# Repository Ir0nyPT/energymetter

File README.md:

# energymetter
contador de energia

# Pre-requesitos
1. Gerar chave no computador para pedir acesso ao github. Após correr o comando, este irá perguntar o ficheiro onde guardar e pass a atribuir, clicar no "Enter" 3 vezes para avançar sem adicionar qualquer valor
> ssh-keygen -t rsa -b 4096

2. Imprimir no terminal a chave gerada
> cat ~/.ssh/id_rsa.pub 

3. Ir ao link abaixo e colar a chave imprimida no último comando no espaço "Key" (chave completa e sem qualquer alteração). Como Título é indiferente o que escreves
https://github.com/settings/ssh/new

4. Clonar o repositório
> git clone git@github.com:Ir0nyPT/energymetter.git

5. Instalar e inicializar 
> cd energymetter

> ./script.sh setup

> ./script.sh init

# Compilar e descarregar
> ./script.sh buildandcopy

OU 

> ./script.sh build

> ./script.sh copy

# Comando disponíveis no script

## Inicializar
> ./script.sh init

## Compilar
> ./script.sh build

## Apagar cache - util para recompilar
> ./script.sh clean

## Enviar para o Pico
> ./script.sh copy

## Obter um terminal de "Debug" (com a ferramenta Minicom)
### Iniciar terminal
> ./script.sh debug
### Terminar terminal
> Press CTRL+A X
### Dar comando para o rasp ir para modo de programação
Com o terminal de debug aberto escrever "reboot" e pressionar enter

# Como guardar algerações?
Antes de iniciar alguma alteração do programa cria um "ramo" do programa
> git checkout -b devop_mj

Após alterações feitas, para reter as alterações
> git add .

Para gravar as alterações. Alterar a "mensagem" por uma breve descrição do que fizes-te
> git commit -m "mensagem"

Para enviar para o github de forma a partilhar
> git push -u origin devop_mj

# Como atualizar com as alterações online?
Desta forma iras obter alterações que outros tenham feito
> git pull 

# Pico W LED
https://github.com/raspberrypi/pico-examples/blob/master/pico_w/wifi/blink/picow_blink.c

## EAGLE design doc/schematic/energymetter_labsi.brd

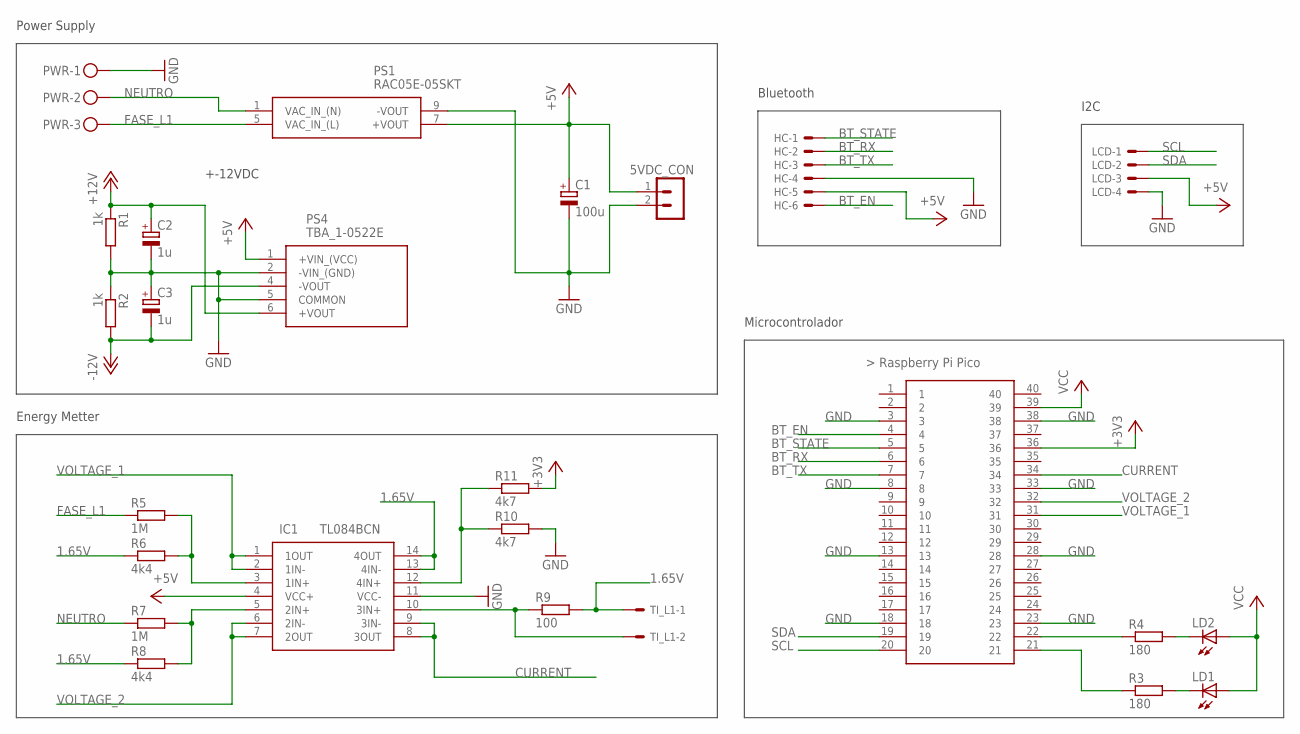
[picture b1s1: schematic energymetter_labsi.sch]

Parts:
5VDC_CON: MA02-1
C1: 100u; E2-5
C2, C3: 1u; E2-5
HC: 22-23-2061
IC1: TL084BCN; DIP794W53P254L1930H508Q14N
LCD: Display; 22-23-2041
LD1, LD2: LED5MM
PS1: RAC05E-05SKT; RAC05E05SKT
PS4: TBA_1-0522E; TBA10522E
PWR: MKDSN1,5/3-5,08
R1, R2: 1k; 0204/7
R3, R4: 180; 0204/7
R5, R7: 1M; 0204/7
R6, R8: 4k4; 0204/7
R9: 100; 0204/7
R10, R11: 4k7; 0204/7
TI_L1: 22-23-2021
U$1: RASPBERRY-PI-PICO_TH; FT_RASPBERRY-PI-PICO_TH

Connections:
1.65V: IC1.13 (4IN-), IC1.14 (4OUT), R6.1, R8.1, R9.2, TI_L1.1
+3V3: R11.2, U$1.36
+5V: 5VDC_CON.1 (2), C1.+, HC.5, IC1.4 (VCC+), LCD.3, PS1.7 (+VOUT), PS4.1 (+VIN_(VCC))
+12V: C2.+, PS4.6 (+VOUT), R1.1
-12V: C3.-, PS4.4 (-VOUT), R2.2
BT_EN: HC.6, U$1.4
BT_RX: HC.2, U$1.6
BT_STATE: HC.1, U$1.5
BT_TX: HC.3, U$1.7
CURRENT: IC1.8 (3OUT), IC1.9 (3IN-), U$1.34
FASE_L1: PS1.5 (VAC_IN_(L)), PWR.3, R5.1
GND: 5VDC_CON.2 (3), C1.-, C2.-, C3.+, HC.4, IC1.11 (VCC-), LCD.4, PS1.9 (-VOUT), PS4.2 (-VIN_(GND)), PS4.5 (COMMON), PWR.1, R1.2, R2.1, R10.2, U$1.3, U$1.8, U$1.13, U$1.18, U$1.23, U$1.28, U$1.33, U$1.38
unnamed: R4.1, U$1.22
unnamed: R3.1, U$1.21
unnamed: LD1.K (C), R3.2
unnamed: LD2.K (C), R4.2
unnamed: IC1.10 (3IN+), R9.1, TI_L1.2
unnamed: IC1.3 (1IN+), R5.2, R6.2
unnamed: IC1.5 (2IN+), R7.2, R8.2
unnamed: IC1.12 (4IN+), R10.1, R11.1
NEUTRO: PS1.1 (VAC_IN_(N)), PWR.2, R7.1
SCL: LCD.1, U$1.20
SDA: LCD.2, U$1.19
VCC: LD1.A, LD2.A, U$1.39
VOLTAGE_1: IC1.1 (1OUT), IC1.2 (1IN-), U$1.31
VOLTAGE_2: IC1.6 (2IN-), IC1.7 (2OUT), U$1.32

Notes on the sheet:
Power Supply
+-12VDC
Microcontrolador
Bluetooth
I2C
Energy Metter

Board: 2 copper layers, 25 parts (0 on the bottom side), 26 nets, no tracks yet.

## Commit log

2023-04-08 Commit inicial - Adição do Pico-SDK como submodulo - Adição de um pequeno programa de base - Adição da opção de poder colocar o micro em modo programação via Serial
2023-04-08 -Criação de uma lib de exemplo para o energymetter
2023-05-20 Ensaio ADC com leitura de temperatura do Pico
2023-05-26 - Obter valores de tensão; - Obter valores de temperatura; - Comunicação entre dois cores;
2023-05-30 Improve script to build: Auto adjust number of jobs with number of CPUs
2023-06-08 WIP
    - Adicionar MQTT client
2023-06-08 Adição da pasta documentação
    - Adição do esquema em eagle
2023-06-17 Leitura de Tensão
    -Limpesa do programa
    -Criação da class para energymetter
    -Leitura de Tensão Fase e Neutro a funcionar
    -Inicio de calculo de frequencia/periodo
2023-07-08 Adição do interrupt timer - Update do contador de energia num periodo conhecido - Led 1 Hz com o interrupt timer
